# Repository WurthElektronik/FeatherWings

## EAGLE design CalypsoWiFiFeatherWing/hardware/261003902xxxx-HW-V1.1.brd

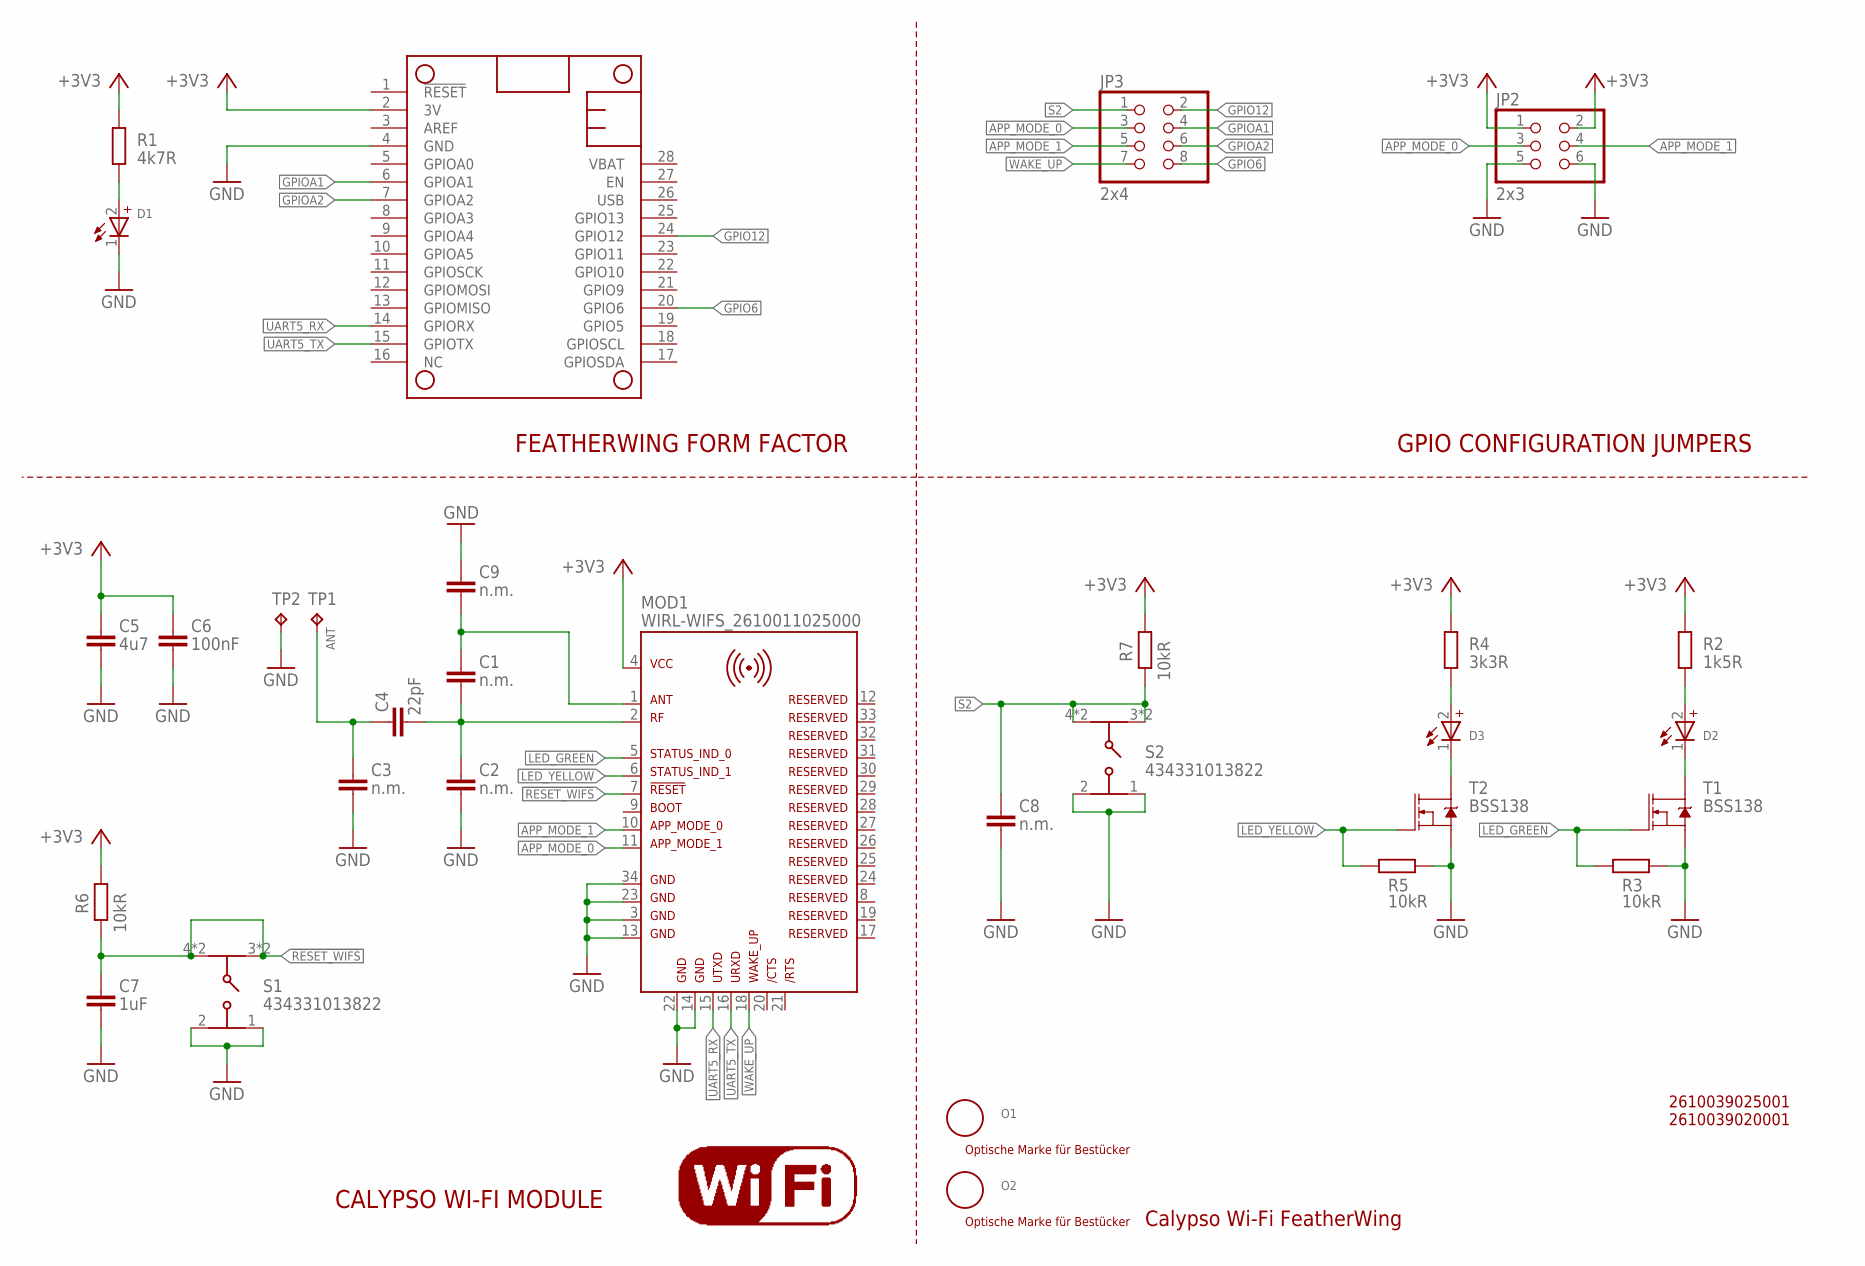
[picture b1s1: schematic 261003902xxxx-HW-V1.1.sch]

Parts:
C1, C8: n.m.; C0402_IPC
C2, C3, C9: n.m.; C0201_IPC
C4: 22pF; C0402_IPC
C5: 4u7; C0402_IPC
C6: 100nF; C0402_IPC
C7: 1uF; C0402_IPC
D1: RED; WL-SMSW_1204_A
D2: GREEN; WL-SMSW_1204_A
D3: YELLOW; WL-SMSW_1204_A
JP2: 2x3; 2X03
JP3: 2x4; 2X04
MOD1: WIRL-WIFS_2610011025000
MS1: header: 1 x 12 & 1 x 16; FEATHERWING_80MM
O1, O2: n.m.; OPTISCHE_MARKE
R1: 4k7R; R0402_IPC
R2: 1k5R; R0402_IPC
R3, R5, R6, R7: 10kR; R0402_IPC
R4: 3k3R; R0402_IPC
S1, S2: 434331013822
T1, T2: BSS138; SOT23-3
TP1, TP2: n.m.; D0.6
U$1: WIFI5MM; WIFI_5MM

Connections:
!RESET_WIFS: C7.1, MOD1.7, R6.1, S1.3, S1.4, S1.5 (3), S1.6 (4)
+3V3: C5.1, C6.1, JP2.1, JP2.2, MOD1.4, MS1.2 (3V), R1.2, R2.2, R4.2, R6.2, R7.2
ANT: C3.P$1 (1), C4.1, TP1.P$1
APP_MODE_0: JP2.3, JP3.3, MOD1.11
APP_MODE_1: JP2.4, JP3.5, MOD1.10
GND: C2.P$2 (2), C3.P$2 (2), C5.2, C6.2, C7.2, C8.2, C9.P$2 (2), D1.1 (-), JP2.5, JP2.6, MOD1.3, MOD1.13, MOD1.14, MOD1.22, MOD1.23, MOD1.34, MS1.4 (GND), R3.1, R5.1, S1.1, S1.2, S2.1, S2.2, T1.2 (S), T2.2 (S), TP2.P$1
GPIO6: JP3.8, MS1.20 (GPIO6)
GPIO12: JP3.2, MS1.24 (GPIO12)
GPIOA1: JP3.4, MS1.6 (GPIOA1)
GPIOA2: JP3.6, MS1.7 (GPIOA2)
LED_GREEN: MOD1.5, R3.2, T1.1 (G)
LED_YELLOW: MOD1.6, R5.2, T2.1 (G)
unnamed: D1.2 (+), R1.1
unnamed: C1.1, C2.P$1 (1), C4.2, MOD1.2
unnamed: C1.2, C9.P$1 (1), MOD1.1
unnamed: D2.2 (+), R2.1
unnamed: D2.1 (-), T1.3 (D)
unnamed: D3.2 (+), R4.1
unnamed: D3.1 (-), T2.3 (D)
S2: C8.1, JP3.1, R7.1, S2.3, S2.4, S2.5 (3), S2.6 (4)
UART5_RX: MOD1.15, MS1.14 (GPIORX)
UART5_TX: MOD1.16, MS1.15 (GPIOTX)
WAKE_UP: JP3.7, MOD1.18

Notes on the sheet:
Calypso Wi-Fi FeatherWing
FEATHERWING FORM FACTOR
CALYPSO WI-FI MODULE
GPIO CONFIGURATION JUMPERS
2610039025001 2610039020001

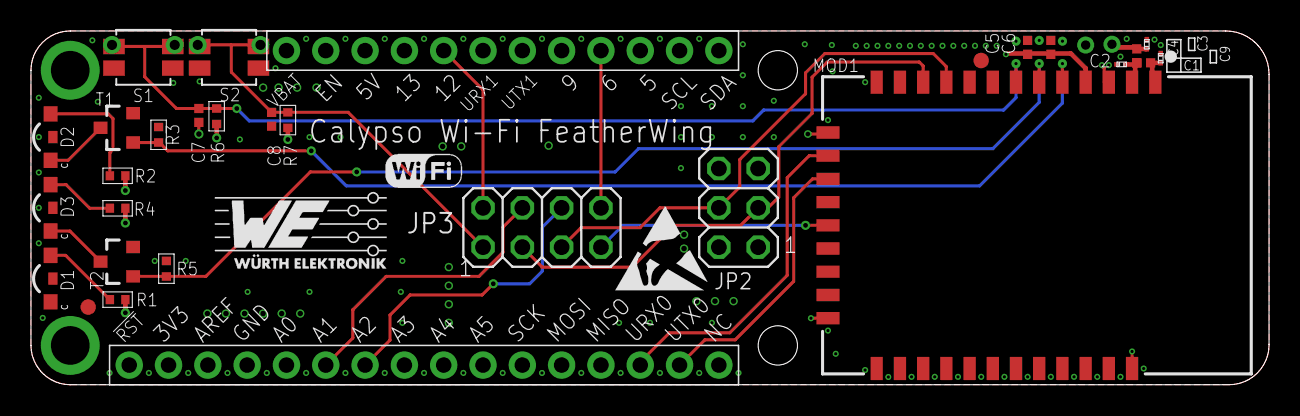
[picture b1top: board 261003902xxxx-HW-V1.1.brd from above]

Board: 4 copper layers, 80.0 x 22.9 mm, 35 parts (1 on the bottom side), 23 nets.

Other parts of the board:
U$2: WE-LOGO-5MM_TNAME
U$4: FEATHER_12MM
U$5: ESD_6MM

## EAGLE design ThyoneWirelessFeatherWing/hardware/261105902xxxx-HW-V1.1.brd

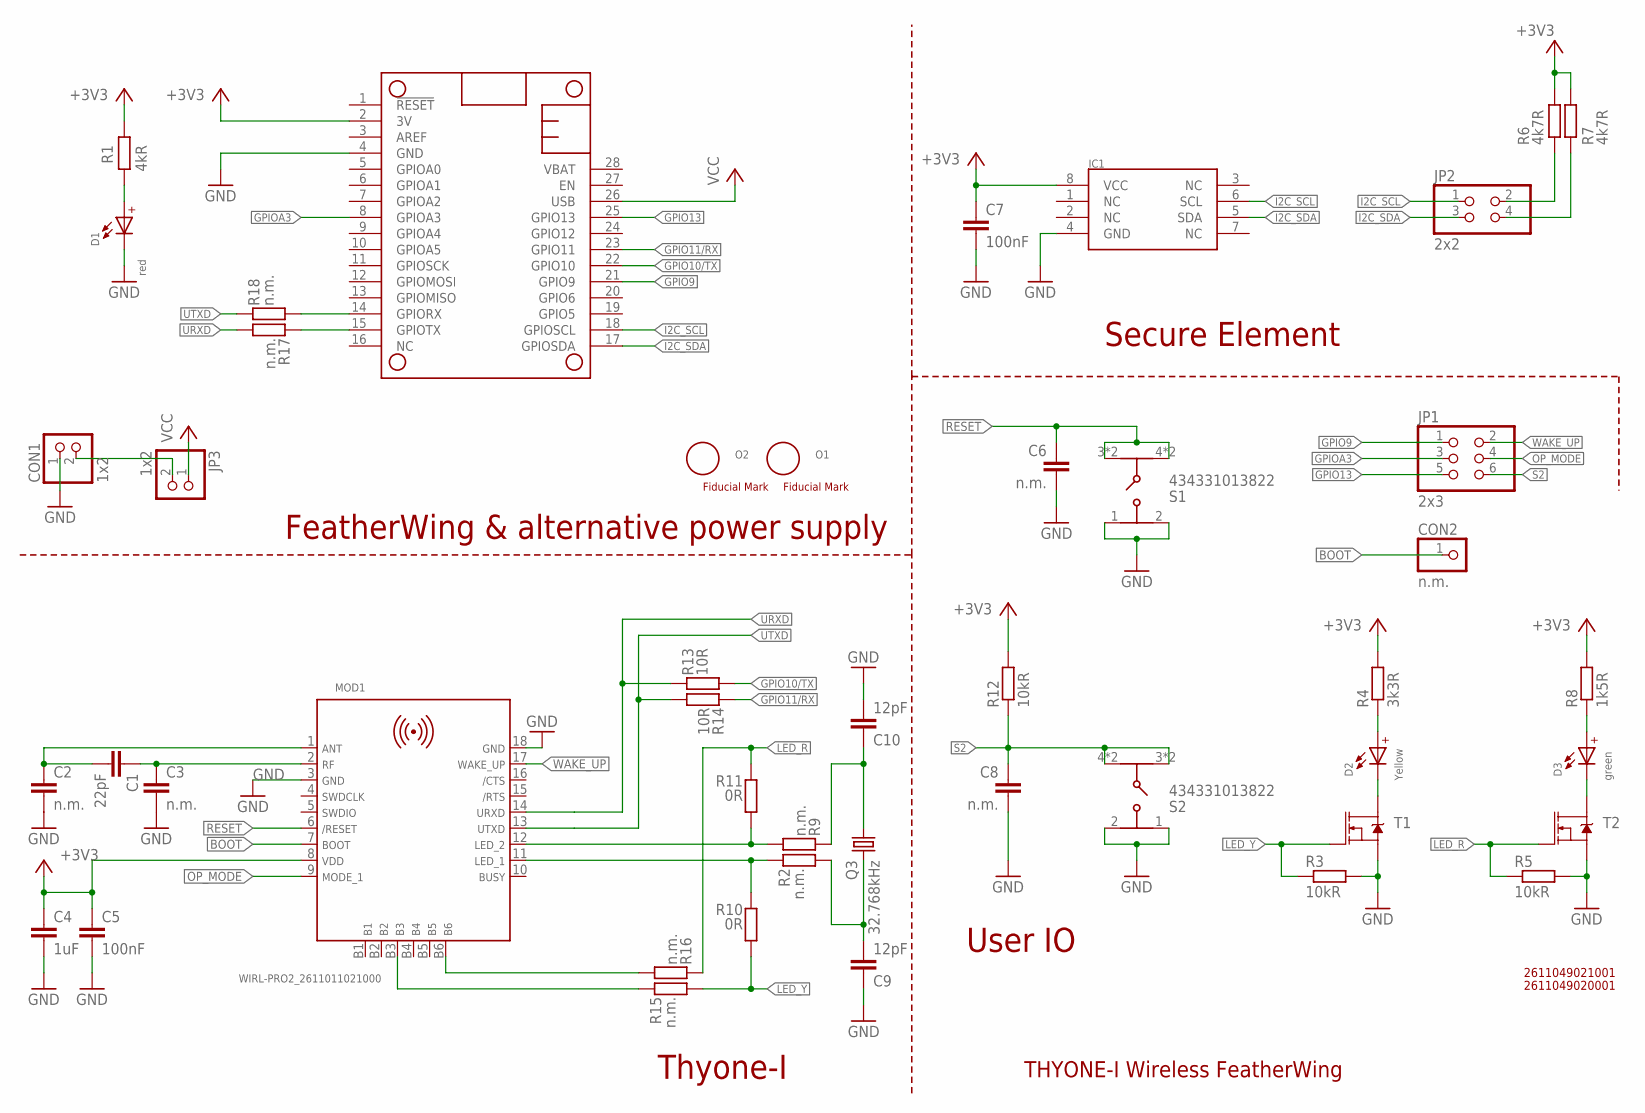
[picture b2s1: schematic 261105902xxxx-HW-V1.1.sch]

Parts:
C1: 22pF; C0402_IPC
C2, C3, C6, C8: n.m.; C0402_IPC
C4: 1uF; C0402_IPC
C5, C7: 100nF; C0402_IPC
C9, C10: 12pF; C0402_IPC
CON1: 1x2; 1X02/R
CON2: n.m.; 1X01/R
D1: red; WL-SMSW_1204_A
D2: Yellow; WL-SMSW_1204_A
D3: green; WL-SMSW_1204_A
IC1: ATECC608A; SOIC127P600X175-8N
JP1: 2x3; 2X03
JP2: 2x2; 2X02
JP3: 1x2; 1X02/R
MOD1: WIRL-PRO2_2611011021000
MS1: header: 1 x 12 & 1 x 16; FEATHERWING
O1, O2: n.m.; OPTISCHE_MARKE
Q3: 32.768kHz; 3216
R1: 4kR; R0402_IPC
R2, R9, R15, R16, R17, R18: n.m.; R0402_IPC
R3, R5, R12: 10kR; R0402_IPC
R4: 3k3R; R0402_IPC
R6, R7: 4k7R; R0402_IPC
R8: 1k5R; R0402_IPC
R10, R11: 0R; R0402_IPC
R13, R14: 10R; R0402_IPC
S1, S2: 434331013822
T1, T2: MOSFET-NCH-BSS138; SOT23-3

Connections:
+3V3: C4.1, C5.1, C7.1, IC1.8 (VCC), MOD1.8 (VDD), MS1.2 (3V), R1.2, R4.2, R6.2, R7.2, R8.2, R12.2
ANT: C1.2, C2.1, MOD1.1 (ANT_PAD)
BOOT: CON2.1, MOD1.7 (P0.02/BOOT)
GND: C2.2, C3.2, C4.2, C5.2, C6.2, C7.2, C8.2, C9.1, C10.2, CON1.1, D1.1 (-), IC1.4 (GND), MOD1.3 (GND), MOD1.18 (GND), MS1.4 (GND), R3.2, R5.2, S1.1, S1.2, S2.1, S2.2, T1.2 (S), T2.2 (S)
GPIO9: JP1.1, MS1.21 (GPIO9)
GPIO10/TX: MS1.22 (GPIO10), R13.2
GPIO11/RX: MS1.23 (GPIO11), R14.1
GPIO13: JP1.5, MS1.25 (GPIO13)
GPIOA3: JP1.3, MS1.8 (GPIOA3)
I2C_SCL: IC1.6 (SCL), JP2.1, MS1.18 (GPIOSCL)
I2C_SDA: IC1.5 (SDA), JP2.3, MS1.17 (GPIOSDA)
LED_R: R5.1, R11.1, R16.1, T2.1 (G)
LED_Y: R3.1, R10.2, R15.2, T1.1 (G)
unnamed: D1.2 (+), R1.1
unnamed: D2.2 (+), R4.1
unnamed: D2.1 (-), T1.3 (D)
unnamed: D3.2 (+), R8.1
unnamed: D3.1 (-), T2.3 (D)
unnamed: JP2.2, R6.1
unnamed: JP2.4, R7.1
unnamed: CON1.2, JP3.2
unnamed: MOD1.12 (P0.01/LED_2), R9.2, R11.2
unnamed: MOD1.11 (P0.00/LED_1), R2.1, R10.1
unnamed: C9.2, Q3.2, R2.2
unnamed: C10.1, Q3.1, R9.1
unnamed: MOD1.B3, R15.1
unnamed: MOD1.B6, R16.2
unnamed: MS1.14 (GPIORX), R18.2
unnamed: MS1.15 (GPIOTX), R17.1
OP_MODE: JP1.4, MOD1.9 (P0.19/MODE_1)
RESET: C6.1, MOD1.6 (P0.18/RESET), S1.3, S1.4, S1.5 (3), S1.6 (4)
RF: C1.1, C3.1, MOD1.2 (RF)
S2: C8.1, JP1.6, R12.1, S2.3, S2.4, S2.5 (3), S2.6 (4)
URXD: MOD1.14 (P1.09/URXD), R13.1, R17.2
UTXD: MOD1.13 (P1.08/UTXD), R14.2, R18.1
VCC: JP3.1, MS1.26 (USB)
WAKE_UP: JP1.2, MOD1.17 (P0.03/WAKE_UP)

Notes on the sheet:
THYONE-I Wireless FeatherWing
User IO
Secure Element
Thyone-I
FeatherWing & alternative power supply
2611049021001
2611049020001

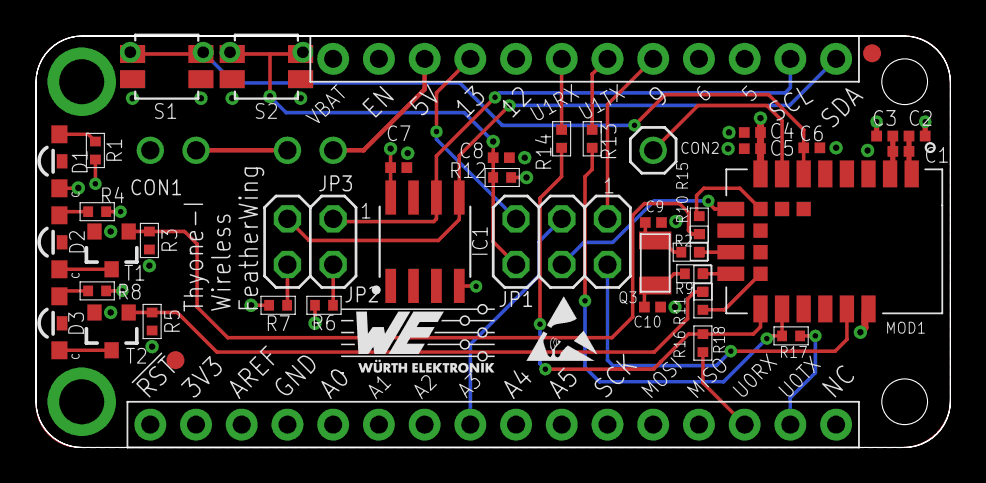
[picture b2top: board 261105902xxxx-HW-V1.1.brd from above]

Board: 4 copper layers, 50.8 x 22.9 mm, 49 parts (1 on the bottom side), 37 nets.

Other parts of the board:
U$1: ESD_4MM
U$2: WE-LOGO-8MM_TNAME
U$3: FEATHER_8MM

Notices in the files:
parts and their libraries:
SparkFun-DiscreteSemi: Licensing: Creative Commons ShareAlike 4.0 International - https://creativecommons.org/licenses/by-sa/4.0
WE_WIRL_Rev1_mod: Copyright: Würth Elektronik
